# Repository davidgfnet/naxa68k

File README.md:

Project naxa68k
===============

aka Late for the Big Day

Contents of the repo
--------------------

 * art: Where the beauty lies. Check the credits for licenses please.
   - golden: Contains images and their XCF Gimp goldens.
   - music: Deflemask tracks, both originals and my remixes.
   - resources: Mostly TMX (Tiled) levels, partially autogenerated and hand tweaked.
   - sound: SXFR parameter files, for the original SFXR (http://drpetter.se/project_sfxr.html) 
 * cart-pcb: Contains the cartridge design (for Eagle CAD) and Gerber files
 * cart-pcb/art: Art & Cover for the cartridge and cart's case.
 * res: Resources for SGDK, contains SFX and Music in VGM/WAV format (later autogenerated into resources.o).
 * src: Source code, mainly .c and .h stuff. assets subdir contains autogenerated art that gets built in.
 * tools: Python code to convert levels/images into game-readable stuff (autogenerates assets).

(Re)-generating assets
----------------------

I checked in all the assets (usually .h files with huge arrays under src/assets) but if you modify
any image you might wanna regenerate (and rebuild) the project for it to get updated. To do that just
run ./resgen.sh. You will need pypy3 (and probably python3 too) and a bunch of libs/deps which might not
be trivial to get, you've been warned! The reason to use pypy3 is that my compressor code takes 50x time
to run if cPython interpreter is used :) I'd probably code that in C++ now but whatever...

Building this
-------------

If you are brave enough of course! I used Linux and SGDK 1.34. In particular I used this repo:
https://github.com/kubilus1/gendev which at the time, was at 1.34 (now seems to be updated to 1.40).
Once that is installed and ready to be used, one just needs to invoke the provided Makefile, which
will build and generate a binary image that can be used in emulators or burned to a cart.

`make -f $GENDEV/sgdk/mkfiles/makefile.gen all`

Where GENDEV points to the SDK directory, usually /opt/gendev

Known bugs
----------

There's so many :) I might release a v1.1 to fix some of the most annoying ones, cause it's a bit of a pain
to play sometimes. There's also some other bugs that are less obvious, in particular mismatches between
game behaviour and what I intended the game to be.

 - Ghosts in the first level should move in a harmonic fashion in the long corridor, otherwise it's too hard.
 - Bomberman game has some invisible collision block, no idea why, but seems to happen consistenly?
 - The dungeon level needs door anims and better UI to signal object collection, it's confusing as it is.
 - Lack of overall life count. Perhaps the arcade level should have its own life counter or infinite tries.
 - A way to jump to credits would be nice.
 - The lack of password restore a game, not a big deal tho due to emulation savestates I guess.

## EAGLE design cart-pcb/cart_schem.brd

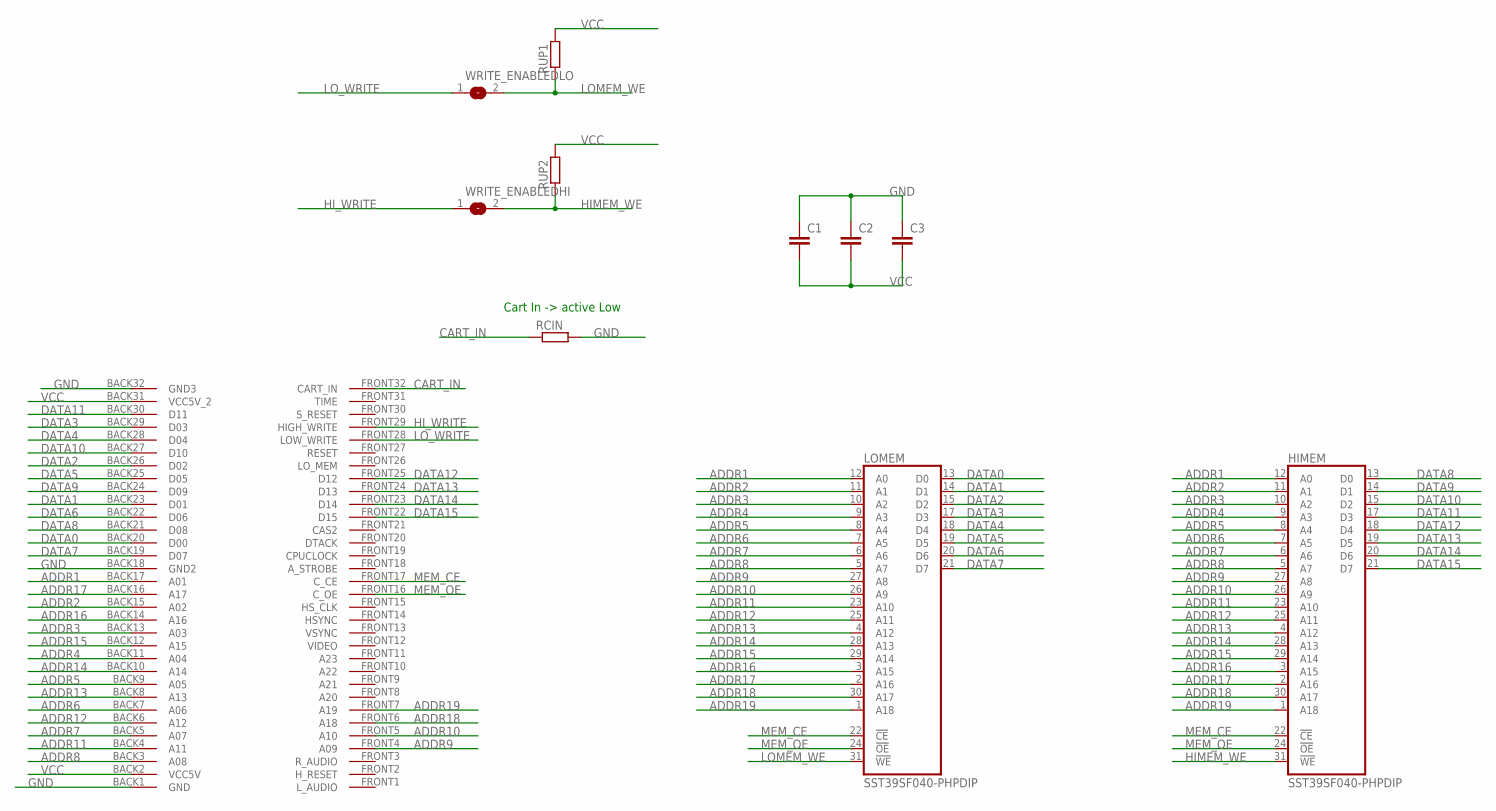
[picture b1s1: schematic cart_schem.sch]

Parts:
C1, C2, C3: C-EU025-024X044; C025-024X044
HIMEM: SST39SF040-PHPDIP; DIL32
LOMEM: SST39SF040-PHPDIP; DIL32
MD1: MEGADRIVE-CART; MEGADRIVE-SLOT-PACKAGE
RCIN: R0207/10; 0207/10
RUP1, RUP2: R0207/10; 0207/10
WRITE_ENABLEDHI: SJ
WRITE_ENABLEDLO: SJ

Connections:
ADDR1: HIMEM.12 (A0), LOMEM.12 (A0), MD1.BACK17 (A01)
ADDR2: HIMEM.11 (A1), LOMEM.11 (A1), MD1.BACK15 (A02)
ADDR3: HIMEM.10 (A2), LOMEM.10 (A2), MD1.BACK13 (A03)
ADDR4: HIMEM.9 (A3), LOMEM.9 (A3), MD1.BACK11 (A04)
ADDR5: HIMEM.8 (A4), LOMEM.8 (A4), MD1.BACK9 (A05)
ADDR6: HIMEM.7 (A5), LOMEM.7 (A5), MD1.BACK7 (A06)
ADDR7: HIMEM.6 (A6), LOMEM.6 (A6), MD1.BACK5 (A07)
ADDR8: HIMEM.5 (A7), LOMEM.5 (A7), MD1.BACK3 (A08)
ADDR9: HIMEM.27 (A8), LOMEM.27 (A8), MD1.FRONT4 (A09)
ADDR10: HIMEM.26 (A9), LOMEM.26 (A9), MD1.FRONT5 (A10)
ADDR11: HIMEM.23 (A10), LOMEM.23 (A10), MD1.BACK4 (A11)
ADDR12: HIMEM.25 (A11), LOMEM.25 (A11), MD1.BACK6 (A12)
ADDR13: HIMEM.4 (A12), LOMEM.4 (A12), MD1.BACK8 (A13)
ADDR14: HIMEM.28 (A13), LOMEM.28 (A13), MD1.BACK10 (A14)
ADDR15: HIMEM.29 (A14), LOMEM.29 (A14), MD1.BACK12 (A15)
ADDR16: HIMEM.3 (A15), LOMEM.3 (A15), MD1.BACK14 (A16)
ADDR17: HIMEM.2 (A16), LOMEM.2 (A16), MD1.BACK16 (A17)
ADDR18: HIMEM.30 (A17), LOMEM.30 (A17), MD1.FRONT6 (A18)
ADDR19: HIMEM.1 (A18), LOMEM.1 (A18), MD1.FRONT7 (A19)
CART_IN: MD1.FRONT32 (CART_IN), RCIN.1
DATA0: LOMEM.13 (D0), MD1.BACK20 (D00)
DATA1: LOMEM.14 (D1), MD1.BACK23 (D01)
DATA2: LOMEM.15 (D2), MD1.BACK26 (D02)
DATA3: LOMEM.17 (D3), MD1.BACK29 (D03)
DATA4: LOMEM.18 (D4), MD1.BACK28 (D04)
DATA5: LOMEM.19 (D5), MD1.BACK25 (D05)
DATA6: LOMEM.20 (D6), MD1.BACK22 (D06)
DATA7: LOMEM.21 (D7), MD1.BACK19 (D07)
DATA8: HIMEM.13 (D0), MD1.BACK21 (D08)
DATA9: HIMEM.14 (D1), MD1.BACK24 (D09)
DATA10: HIMEM.15 (D2), MD1.BACK27 (D10)
DATA11: HIMEM.17 (D3), MD1.BACK30 (D11)
DATA12: HIMEM.18 (D4), MD1.FRONT25 (D12)
DATA13: HIMEM.19 (D5), MD1.FRONT24 (D13)
DATA14: HIMEM.20 (D6), MD1.FRONT23 (D14)
DATA15: HIMEM.21 (D7), MD1.FRONT22 (D15)
GND: C1.1, C2.1, C3.1, HIMEM.16 (GND), LOMEM.16 (GND), MD1.BACK1 (GND), MD1.BACK18 (GND2), MD1.BACK32 (GND3), RCIN.2
HIMEM_WE: HIMEM.31 (!WE), RUP2.1, WRITE_ENABLEDHI.2
HI_WRITE: MD1.FRONT29 (HIGH_WRITE), WRITE_ENABLEDHI.1
LOMEM_WE: LOMEM.31 (!WE), RUP1.1, WRITE_ENABLEDLO.2
LO_WRITE: MD1.FRONT28 (LOW_WRITE), WRITE_ENABLEDLO.1
MEM_CE: HIMEM.22 (!CE), LOMEM.22 (!CE), MD1.FRONT17 (C_CE)
MEM_OE: HIMEM.24 (!OE), LOMEM.24 (!OE), MD1.FRONT16 (C_OE)
VCC: C1.2, C2.2, C3.2, HIMEM.32 (VCC), LOMEM.32 (VCC), MD1.BACK2 (VCC5V), MD1.BACK31 (VCC5V_2), RUP1.2, RUP2.2

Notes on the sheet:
Cart In -> active Low

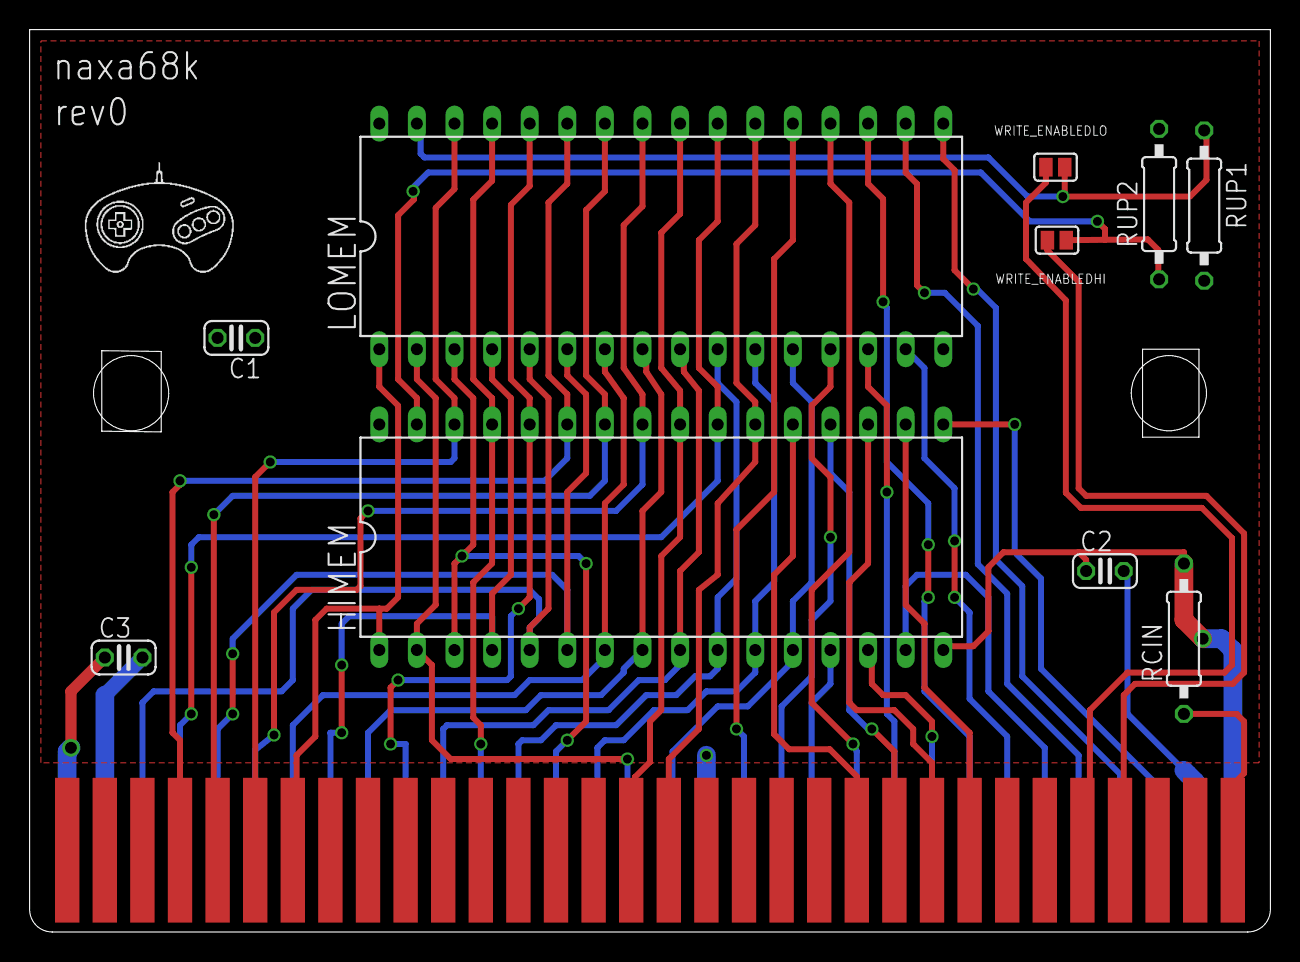
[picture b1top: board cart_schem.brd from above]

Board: 2 copper layers, 83.8 x 61.0 mm, 11 parts (0 on the bottom side), 44 nets.

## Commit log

2019-09-17 Squash all commits, let's not reveal history :)
2019-09-17 Add readme
2019-09-17 Ooops update incomplete README
